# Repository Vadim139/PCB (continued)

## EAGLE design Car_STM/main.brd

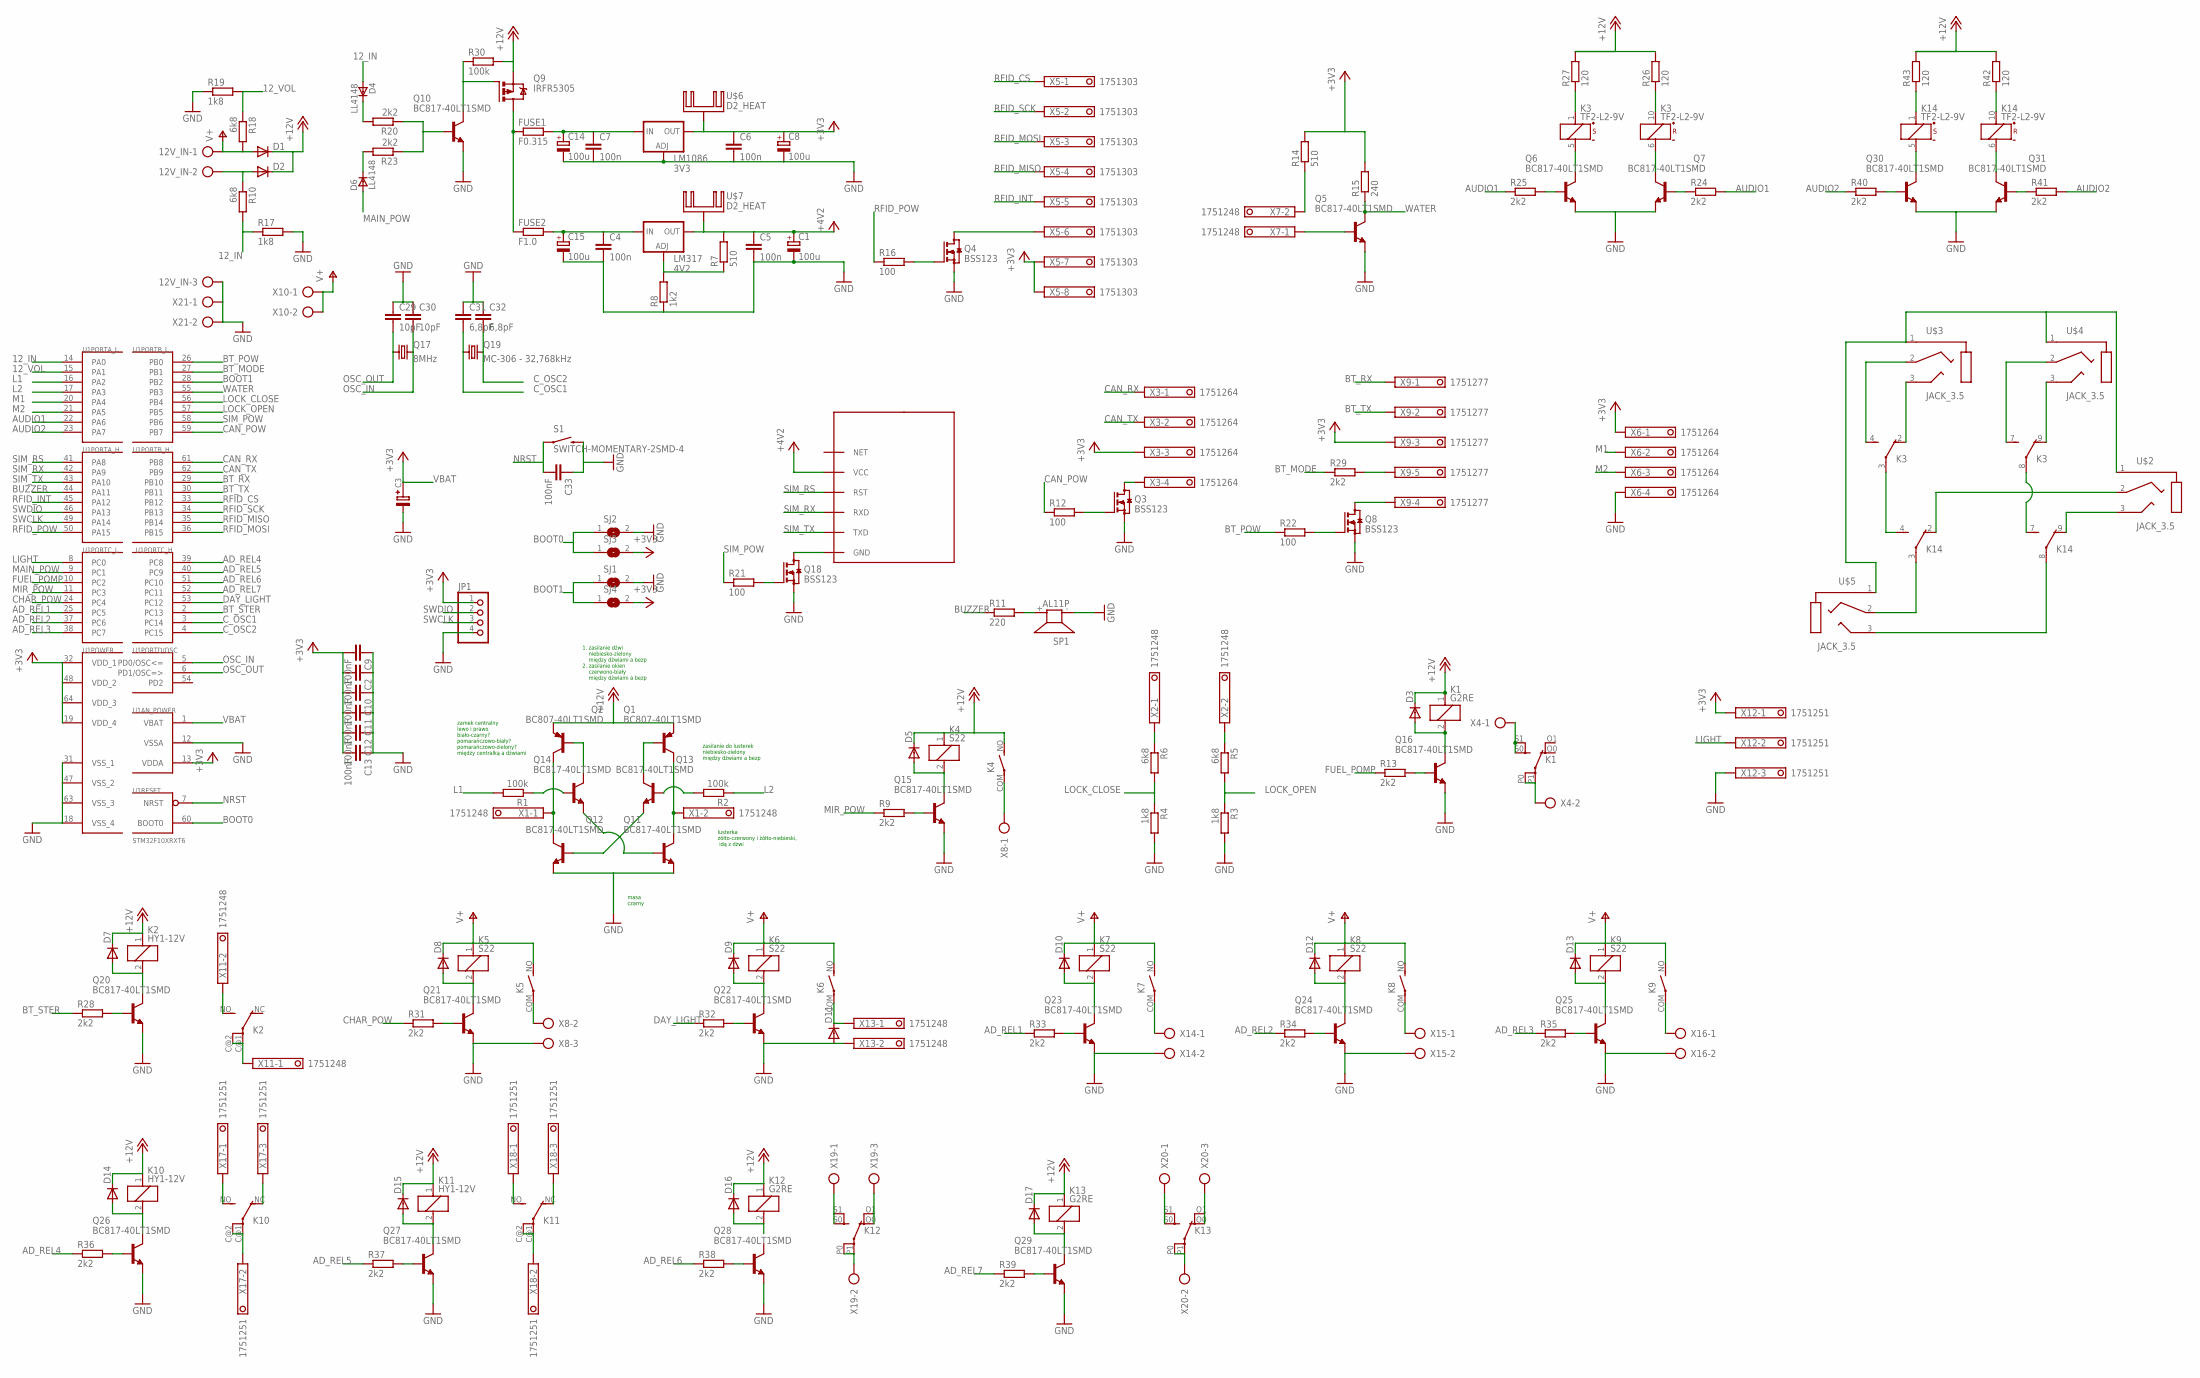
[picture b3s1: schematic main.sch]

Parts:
12V_IN: AK500/3
C1, C8, C14, C15: 100u; E2,5-6E
C2, C9, C10, C11, C12, C13, C33: 100nF; C2012
C3: CAP-13,5; PAC-G-1
C4, C5, C6, C7: 100n; C2012
C29, C30: 10pF; C2012
C31, C32: 6,8pF; C2012
D1, D2: DIODE-P6-15; P6-15
D3, D5, D7, D8, D9, D10, D11, D12, D13, D14, D15, D16, D17: DIODE-DO-214AC; DO-214AC
D4, D6: LL4148; SOD80_DO213AA_MINIMELF
FUSE1: F0.315; R2512
FUSE2: F1.0; R2512
JP1: PINHD-1X4; 1X04
K1, K12, K13: G2RE
K2, K10, K11: HY1-12V; HY
K3, K14: TF2-L2-9V; TF2
K4, K5, K6, K7, K8, K9: S22; LD
LM317: 4V2; D2PACK
LM1086: 3V3; D2PACK
Q1, Q2: BC807-40LT1SMD; SOT23-BEC
Q3, Q4, Q8, Q18: BSS123; SOT23
Q5, Q6, Q7, Q10, Q11, Q12, Q13, Q14, Q15, Q16, Q20, Q21, Q22, Q23, Q24, Q25, Q26, Q27, Q28, Q29, Q30, Q31: BC817-40LT1SMD; SOT23-BEC
Q9: IRFR5305; D-PAK_TO252AA
Q17: 8MHz; HC49UP
Q19: MC-306 - 32,768kHz; MC-306
R1, R2, R30: 100k; R0805
R3, R4, R17, R19: 1k8; R0805
R5, R6, R10, R18: 6k8; R0805
R7: 510; 0204/7
R8: 1k2; 0204/7
R9, R13, R20, R23, R24, R25, R28, R29, R31, R32, R33, R34, R35, R36, R37, R38, R39, R40, R41: 2k2; R0805
R11: 220; 0204/7
R12, R16, R21, R22: 100; R0805
R14: 510; R0805
R15: 240; R0805
R26, R27, R42, R43: 120; R0805
S1: SWITCH-MOMENTARY-2SMD-4; TACTILE_SWITCH_TALL
SJ1, SJ2, SJ3, SJ4: SJ
SP1: AL11P
U1: STM32F10XRXT6; TQFP64
U$1: SIM800L; SIM-CORE
U$2, U$3, U$4, U$5: JACK_3.5; STX3100
U$6, U$7: D2_HEAT; D2PACK_HEATSINK
X1, X2, X7, X11, X13: 1751248
X3, X6: 1751264
X4, X10, X14, X15, X16, X21: AK500/2
X5: 1751303
X8, X19, X20: AK500/3
X9: 1751277
X12, X17, X18: 1751251

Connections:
4V2: U$1.VCC
12_IN: D4.A, R10.2, R17.1, U1.14 (PA0)
12_VOL: R18.1, R19.2, U1.15 (PA1)
+3V3: C2.2, C6.1, C8.+, C9.2, C10.2, C11.2, C12.2, C13.2, JP1.1, LM1086.2 (OUT), R14.2, R15.2, SJ3.2, SJ4.2, U1.13 (VDDA), U1.19 (VDD_4), U1.32 (VDD_1), U1.48 (VDD_2), U1.64 (VDD_3), U$6.1, X3.3, X5.7, X5.8, X6.1, X9.3, X12.1
+12V: D1.C, D2.C, D3.C, D5.C, D7.C, D14.C, D15.C, D16.C, D17.C, K1.1, K2.1, K4.1, K4.NO (S), K10.1, K11.1, K12.1, K13.1, Q1.E, Q2.E, Q9.3 (S), R26.2, R27.2, R30.2, R42.2, R43.2
AD_REL1: R33.1, U1.25 (PC5)
AD_REL2: R34.1, U1.37 (PC6)
AD_REL3: R35.1, U1.38 (PC7)
AD_REL4: R36.1, U1.39 (PC8)
AD_REL5: R37.1, U1.40 (PC9)
AD_REL6: R38.1, U1.51 (PC10)
AD_REL7: R39.1, U1.52 (PC11)
AUDIO1: R24.2, R25.1, U1.22 (PA6)
AUDIO2: R40.1, R41.2, U1.23 (PA7)
BOOT0: SJ2.1, SJ3.1, U1.60 (BOOT0)
BOOT1: SJ1.1, SJ4.1, U1.28 (PB2)
BT_MODE: R29.1, U1.27 (PB1)
BT_POW: R22.1, U1.26 (PB0)
BT_RX: U1.29 (PB10), X9.1
BT_STER: R28.1, U1.2 (PC13)
BT_TX: U1.30 (PB11), X9.2
BUZZER: R11.1, U1.44 (PA11)
CAN_POW: R12.1, U1.59 (PB7)
CAN_RX: U1.61 (PB8), X3.1
CAN_TX: U1.62 (PB9), X3.2
CHAR_POW: R31.1, U1.24 (PC4)
C_OSC1: C31.2, Q19.1, U1.3 (PC14)
C_OSC2: C32.2, Q19.4 (2), U1.4 (PC15)
DAY_LIGHT: R32.1, U1.53 (PC12)
FUEL_POMP: R13.1, U1.10 (PC2)
GND: 12V_IN.3, C1.-, C2.1, C3.-, C4.2, C5.2, C6.2, C7.2, C8.-, C9.1, C10.1, C11.1, C12.1, C13.1, C14.-, C15.-, C29.1, C30.1, C31.1, C32.1, C33.1, D11.A, JP1.4, LM1086.1 (ADJ), Q3.2 (S), Q4.2 (S), Q5.E, Q6.E, Q7.E, Q8.2 (S), Q10.E, Q11.E, Q12.E, Q15.E, Q16.E, Q18.2 (S), Q20.E, Q21.E, Q22.E, Q23.E, Q24.E, Q25.E, Q26.E, Q27.E, Q28.E, Q29.E, Q30.E, Q31.E, R3.2, R4.2, R8.1, R17.2, R19.1, S1.B2 (2), SJ1.2, SJ2.2, SP1.- (1), U1.12 (VSSA), U1.18 (VSS_4), U1.31 (VSS_1), U1.47 (VSS_2), U1.63 (VSS_3), X6.4, X8.3, X12.3, X13.2, X14.2, X15.2, X16.2, X21.1, X21.2
L1: R1.2, U1.16 (PA2)
L2: R2.1, U1.17 (PA3)
LIGHT: U1.8 (PC0), X12.2
LOCK_CLOSE: R4.1, R6.2, U1.56 (PB4)
LOCK_OPEN: R3.1, R5.2, U1.57 (PB5)
M1: U1.20 (PA4), X6.2
M2: U1.21 (PA5), X6.3
MAIN_POW: D6.A, U1.9 (PC1)
MIR_POW: R9.1, U1.11 (PC3)
unnamed: 12V_IN.2, D2.A, R10.1
unnamed: R6.1, X2.1
unnamed: Q1.C, Q11.C, X1.2
unnamed: Q2.C, Q12.C, X1.1
unnamed: R5.1, X2.2
unnamed: Q2.B, Q14.C
unnamed: Q1.B, Q13.C
unnamed: Q12.B, Q13.E
unnamed: D4.C, R20.2
unnamed: R11.2, SP1.+ (2)
unnamed: Q3.1 (G), R12.2
unnamed: Q8.1 (G), R22.2
unnamed: LM317.1 (ADJ), R7.1, R8.2
unnamed: Q3.3 (D), X3.4
unnamed: D3.A, K1.2, Q16.C
unnamed: Q16.B, R13.2
unnamed: K1.S0 (S), K1.S1 (S), X4.1
unnamed: K1.P0, K1.P1, X4.2
unnamed: R14.1, X7.2
unnamed: Q4.3 (D), X5.6
unnamed: K14.1 (+), R43.1
unnamed: Q14.B, R1.1
unnamed: Q5.B, X7.1
unnamed: Q13.B, R2.2
unnamed: Q11.B, Q14.E
unnamed: Q4.1 (G), R16.2
unnamed: Q15.B, R9.2
unnamed: D5.A, K4.2, Q15.C
unnamed: K14.10 (+), R42.1
unnamed: K14.5 (-), Q30.C
unnamed: K14.6 (-), Q31.C
unnamed: Q30.B, R40.2
unnamed: K3.1 (+), R27.1
unnamed: K3.10 (+), R26.1
unnamed: K3.5 (-), Q6.C
unnamed: K3.6 (-), Q7.C
unnamed: Q6.B, R25.2
unnamed: Q8.3 (D), X9.4
unnamed: FUSE1.1, FUSE2.1, Q9.4 (D)
unnamed: Q7.B, R24.1
unnamed: R29.2, X9.5
unnamed: Q10.B, R20.1, R23.1
unnamed: Q9.1 (G), Q10.C, R30.1
unnamed: D6.C, R23.2
unnamed: C7.1, C14.+, FUSE1.2, LM1086.3 (IN)
unnamed: Q18.3 (D), U$1.GND
unnamed: K4.COM, X8.1
unnamed: C4.1, C15.+, FUSE2.2, LM317.3 (IN)
unnamed: Q31.B, R41.1
unnamed: Q18.1 (G), R21.2
unnamed: D7.A, K2.2, Q20.C
unnamed: Q20.B, R28.2
unnamed: D11.C, K6.COM, X13.1
unnamed: Q26.B, R36.2
unnamed: D8.A, K5.2, Q21.C
unnamed: K2.NO (S), X11.2
unnamed: K2.C@1, K2.C@2, X11.1
unnamed: Q21.B, R31.2
unnamed: D9.A, K6.2, Q22.C
unnamed: Q22.B, R32.2
unnamed: D10.A, K7.2, Q23.C
unnamed: Q23.B, R33.2
unnamed: K5.COM, X8.2
unnamed: K7.COM, X14.1
unnamed: D14.A, K10.2, Q26.C
unnamed: D12.A, K8.2, Q24.C
unnamed: Q24.B, R34.2
unnamed: K8.COM, X15.1
unnamed: Q27.B, R37.2
unnamed: D13.A, K9.2, Q25.C
unnamed: Q25.B, R35.2
unnamed: K9.COM, X16.1
unnamed: D15.A, K11.2, Q27.C
unnamed: Q28.B, R38.2
unnamed: K10.NO (S), X17.1
unnamed: Q29.B, R39.2
unnamed: D17.A, K13.2, Q29.C
unnamed: K10.NC (O), X17.3
unnamed: D16.A, K12.2
unnamed: K10.C@1, K10.C@2, X17.2
unnamed: K11.NO (S), X18.1
unnamed: K11.NC (O), X18.3
unnamed: K11.C@1, K11.C@2, X18.2
unnamed: K12.S0 (S), K12.S1 (S), X19.1
unnamed: K12.O0 (O), K12.O1 (O), X19.3
unnamed: K12.P0, K12.P1, X19.2
unnamed: K13.S0 (S), K13.S1 (S), X20.1
unnamed: K13.O0 (O), K13.O1 (O), X20.3
unnamed: K13.P0, K13.P1, X20.2
unnamed: K14.2 (O), U$2.2
unnamed: K14.9 (O), U$2.3 (5)
unnamed: K3.8, K14.7 (S)
unnamed: K3.3, K14.4 (S)
unnamed: K3.4 (S), U$3.2
unnamed: K3.2 (O), U$3.3 (5)
unnamed: K3.7 (S), U$4.2
unnamed: K3.9 (O), U$4.3 (5)
unnamed: U$2.1, U$3.1, U$4.1, U$5.1
unnamed: K14.3, U$5.2
unnamed: K14.8, U$5.3 (5)
NRST: C33.2, S1.A2 (1), U1.7 (NRST)
OSC_IN: C30.2, Q17.2, U1.5 (PD0/OSC<=)
OSC_OUT: C29.2, Q17.1, U1.6 (PD1/OSC=>)
RFID_CS: U1.33 (PB12), X5.1
RFID_INT: U1.45 (PA12), X5.5
RFID_MISO: U1.35 (PB14), X5.4
RFID_MOSI: U1.36 (PB15), X5.3
RFID_POW: R16.1, U1.50 (PA15)
RFID_SCK: U1.34 (PB13), X5.2
SIM_POW: R21.1, U1.58 (PB6)
SIM_RS: U1.41 (PA8), U$1.RST
SIM_RX: U1.42 (PA9), U$1.RXD
SIM_TX: U1.43 (PA10), U$1.TXD
SWCLK: JP1.3, U1.49 (PA14)
SWDIO: JP1.2, U1.46 (PA13)
V+: 12V_IN.1, D1.A, D8.C, D9.C, D10.C, D12.C, D13.C, K5.1, K5.NO (S), K6.1, K6.NO (S), K7.1, K7.NO (S), K8.1, K8.NO (S), K9.1, K9.NO (S), R18.2, X10.1, X10.2
VBAT: C3.+, U1.1 (VBAT)
VCC: C1.+, C5.1, LM317.2 (OUT), R7.2, U$7.1
WATER: Q5.C, R15.1, U1.55 (PB3)

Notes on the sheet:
lusterka żółto-czerwony i żółto-niebieski, idą z dżwi
zasilanie do lusterek niebiesko-zielony między dżwiami a bezp
1. zasilanie dżwi niebiesko-zielony między dżwiami a bezp 2. zasilanie okien czerwono-biały między dżwiami a bezp
zamek centralny lewo i prawo biało-czarny? pomarańczowo-biały? pomarańczowo-zielony? między centralką a dżwiami
masa czarny

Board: 2 copper layers, 166 parts (8 on the bottom side), 158 nets, no tracks yet.

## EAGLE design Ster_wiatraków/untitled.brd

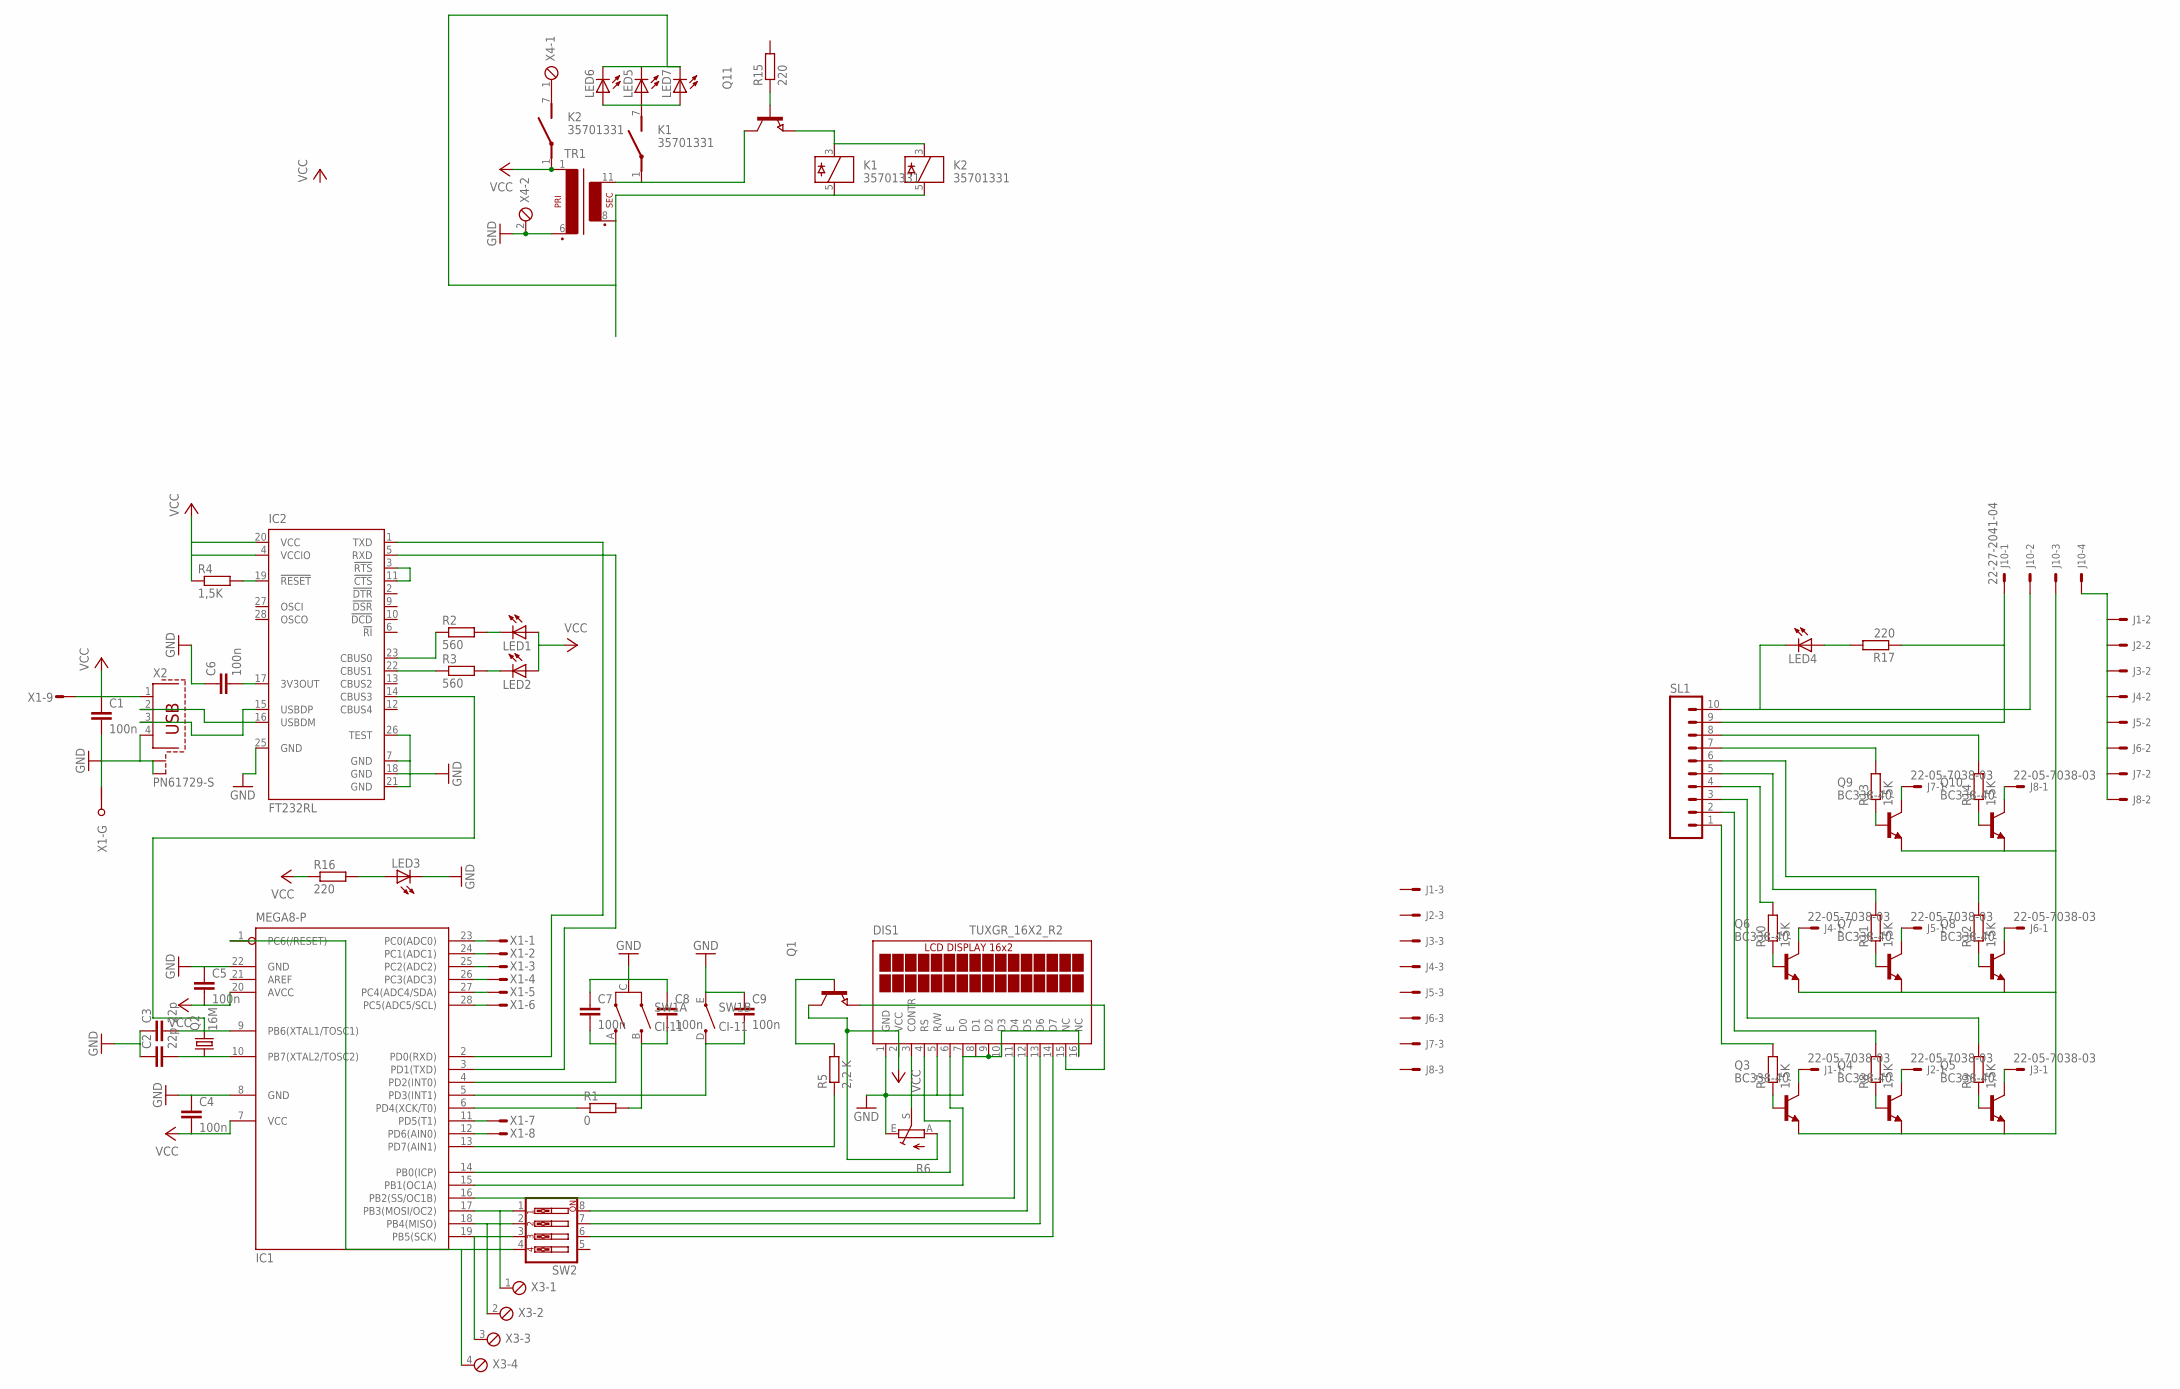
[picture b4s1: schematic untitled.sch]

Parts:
C1, C4, C5, C6: 100n; C0603
C2, C3: 22p; C050-024X044
C7, C8, C9: 100n; C050-024X044
DIS1: TUXGR_16X2_R2
IC1: MEGA8-P; DIL28-3
IC2: FT232RL; SSOP28
J1, J2, J3, J4, J5, J6, J7, J8: 22-05-7038-03; 7395-03
J10: 22-27-2041-04; 6410-04
K1, K2: 35701331; REED
LED1, LED2: LEDCHIPLED_0805; CHIPLED_0805
LED3, LED4, LED5, LED6, LED7: LED5MM
Q1, Q11: NPN-TRANSISTOR_SOT23; SOT23
Q2: 16M; HC49U-V
Q3, Q4, Q5, Q6, Q7, Q8, Q9, Q10: BC338-40; TO92-EBC
R1: 0; M1206
R2, R3: 560; M1406
R4, R7, R8, R9, R10, R11, R12, R13, R14: 1,5K; 0204/5
R5: 2,2 K; 0204/7
R6: TRIM_EU-CA6V; CA6V
R15, R16, R17: 220; 0204/7
SL1: M10; 10P
SW1: CI-11
SW2: SW_DIP-4; EDG-04
TR1: EI48-1
X1: M09VPS; M09VP
X2: PN61729-S
X3, X4: MPT4; 4POL254

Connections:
GND: C1.2, C2.1, C3.1, C4.1, C5.1, C6.1, C7.1, C8.1, C9.1, DIS1.1 (GND), DIS1.5 (R/W), DIS1.7 (D0), DIS1.8 (D1), DIS1.9 (D2), DIS1.10 (D3), DIS1.16 (NC), IC1.8 (GND), IC1.22 (GND), IC2.7 (GND), IC2.18 (GND), IC2.21 (GND), IC2.25 (GND), IC2.26 (TEST), LED3.K (C), R6.E, SW1.C, SW1.E, TR1.6 (P2), X1.G1, X2.4, X2.S1, X2.S2, X4.2
unnamed: IC1.11 (PD5(T1)), X1.7 (M)
unnamed: IC1.6 (PD4(XCK/T0)), R1.1
unnamed: LED5.K (C), LED6.K (C), LED7.K (C)
unnamed: Q11.1 (B), R15.1
unnamed: K1.1, Q11.3 (C), TR1.11 (S4)
unnamed: K1.3, K2.3, Q11.2 (E)
unnamed: K1.5, K2.5, TR1.8 (S3)
unnamed: IC2.16 (USBDM), X2.2
unnamed: IC2.15 (USBDP), X2.3
unnamed: DIS1.3 (CONTR), R6.S
unnamed: DIS1.4 (RS), IC1.14 (PB0(ICP))
unnamed: DIS1.6 (E), IC1.15 (PB1(OC1A))
unnamed: DIS1.11 (D4), IC1.16 (PB2(SS/OC1B))
unnamed: DIS1.12 (D5), SW2.8
unnamed: DIS1.13 (D6), SW2.7
unnamed: DIS1.14 (D7), SW2.6
unnamed: IC1.13 (PD7(AIN1)), R5.1
unnamed: Q1.1 (B), R5.2
unnamed: DIS1.15 (NC), Q1.2 (E)
unnamed: C3.2, IC1.9 (PB6(XTAL1/TOSC1)), IC2.14 (CBUS3), Q2.2
unnamed: C6.2, IC2.17 (3V3OUT)
unnamed: C2.2, IC1.10 (PB7(XTAL2/TOSC2)), Q2.1
unnamed: LED1.C, R2.2
unnamed: LED2.C, R3.2
unnamed: IC2.19 (!RESET), R4.2
unnamed: IC2.23 (CBUS0), R2.1
unnamed: IC2.22 (CBUS1), R3.1
unnamed: IC2.3 (!RTS), IC2.11 (!CTS)
unnamed: IC1.2 (PD0(RXD)), IC2.1 (TXD)
unnamed: IC1.3 (PD1(TXD)), IC2.5 (RXD)
unnamed: IC1.1 (PC6(/RESET)), SW2.4, X3.4
unnamed: IC1.23 (PC0(ADC0)), X1.1 (M)
unnamed: IC1.24 (PC1(ADC1)), X1.2 (M)
unnamed: IC1.25 (PC2(ADC2)), X1.3 (M)
unnamed: IC1.26 (PC3(ADC3)), X1.4 (M)
unnamed: IC1.27 (PC4(ADC4/SDA)), X1.5 (M)
unnamed: IC1.28 (PC5(ADC5/SCL)), X1.6 (M)
unnamed: IC1.12 (PD6(AIN0)), X1.8 (M)
unnamed: IC1.17 (PB3(MOSI/OC2)), SW2.1, X3.1
unnamed: IC1.18 (PB4(MISO)), SW2.2, X3.2
unnamed: IC1.19 (PB5(SCK)), SW2.3, X3.3
unnamed: K1.7 (S), LED5.A, LED6.A, LED7.A
unnamed: C9.2, IC1.5 (PD3(INT1)), SW1.D
unnamed: C7.2, IC1.4 (PD2(INT0)), SW1.A
unnamed: C8.2, R1.2, SW1.B
unnamed: J1.1, Q3.C
unnamed: J2.1, Q4.C
unnamed: K2.7 (S), X4.1
unnamed: LED3.A, R16.2
unnamed: J10.1, R17.1, SL1.9
unnamed: LED4.A, R17.2
unnamed: J10.2, LED4.K (C), SL1.10
unnamed: J3.1, Q5.C
unnamed: J6.1, Q8.C
unnamed: J5.1, Q7.C
unnamed: J4.1, Q6.C
unnamed: J7.1, Q9.C
unnamed: J8.1, Q10.C
unnamed: R7.2, SL1.1
unnamed: Q3.B, R7.1
unnamed: R8.2, SL1.2
unnamed: Q4.B, R8.1
unnamed: R9.2, SL1.3
unnamed: R10.2, SL1.4
unnamed: R11.2, SL1.5
unnamed: R12.2, SL1.6
unnamed: R13.2, SL1.7
unnamed: R14.2, SL1.8
unnamed: Q9.B, R13.1
unnamed: Q10.B, R14.1
unnamed: Q8.B, R12.1
unnamed: Q7.B, R11.1
unnamed: Q6.B, R10.1
unnamed: Q5.B, R9.1
unnamed: J1.2, J2.2, J3.2, J4.2, J5.2, J6.2, J7.2, J8.2, J10.4
unnamed: J10.3, Q3.E, Q4.E, Q5.E, Q6.E, Q7.E, Q8.E, Q9.E, Q10.E
VCC: C1.1, C4.2, C5.2, DIS1.2 (VCC), IC1.7 (VCC), IC1.20 (AVCC), IC2.4 (VCCIO), IC2.20 (VCC), K2.1, LED1.A, LED2.A, Q1.3 (C), R4.1, R6.A, R16.1, TR1.1, X1.9 (M), X2.1

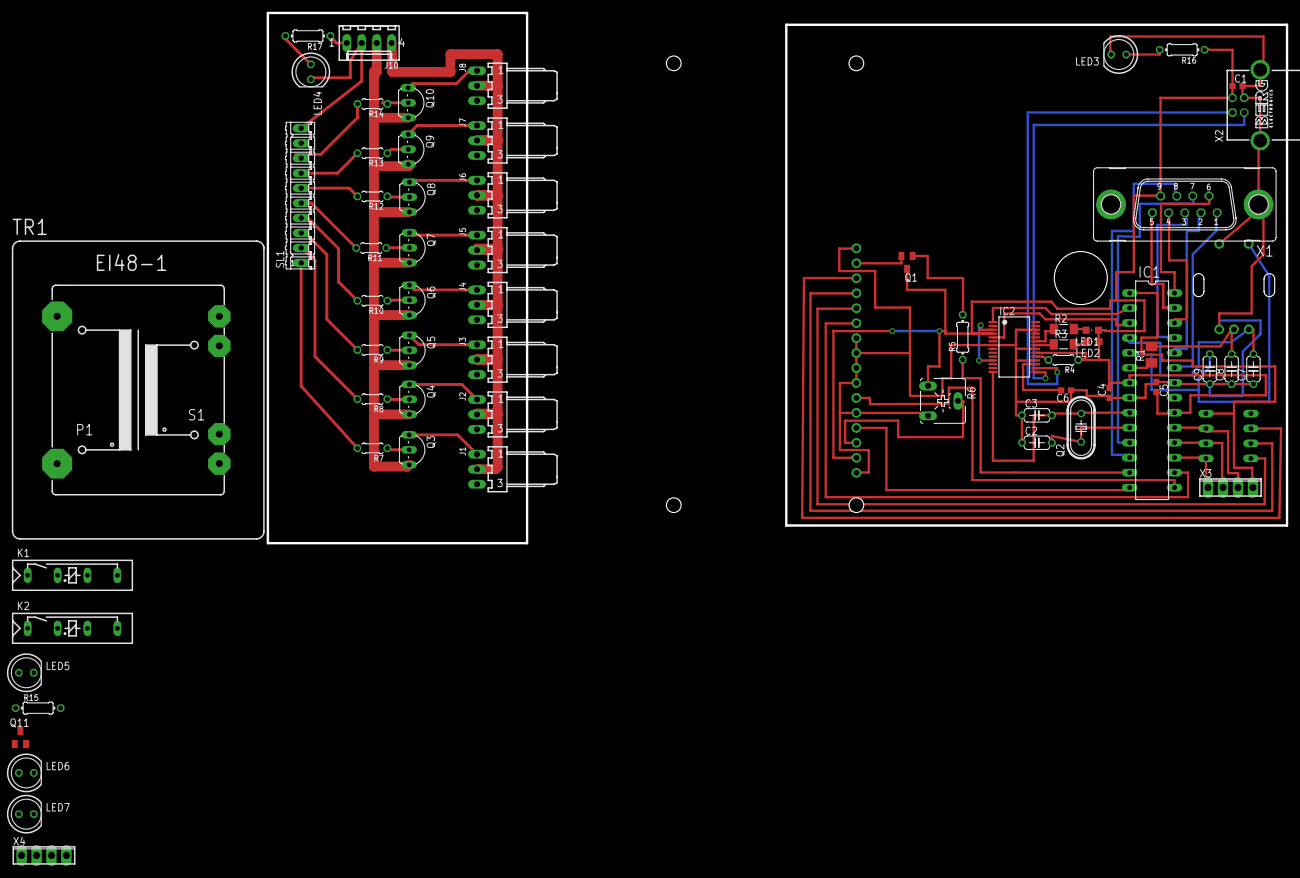
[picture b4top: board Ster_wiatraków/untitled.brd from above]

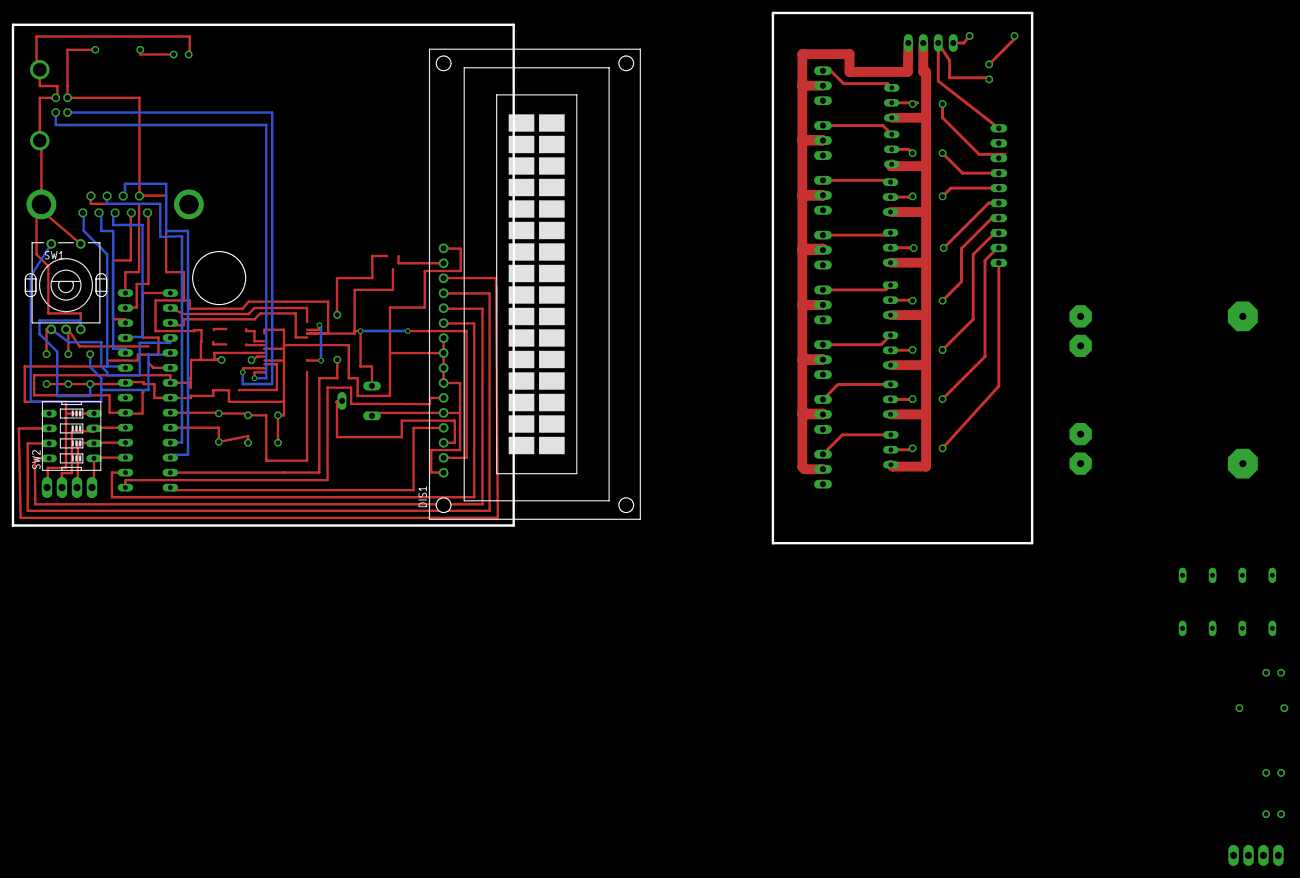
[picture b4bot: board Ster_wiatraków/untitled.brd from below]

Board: 2 copper layers, 173.0 x 90.0 mm, 66 parts (3 on the bottom side), 78 nets.

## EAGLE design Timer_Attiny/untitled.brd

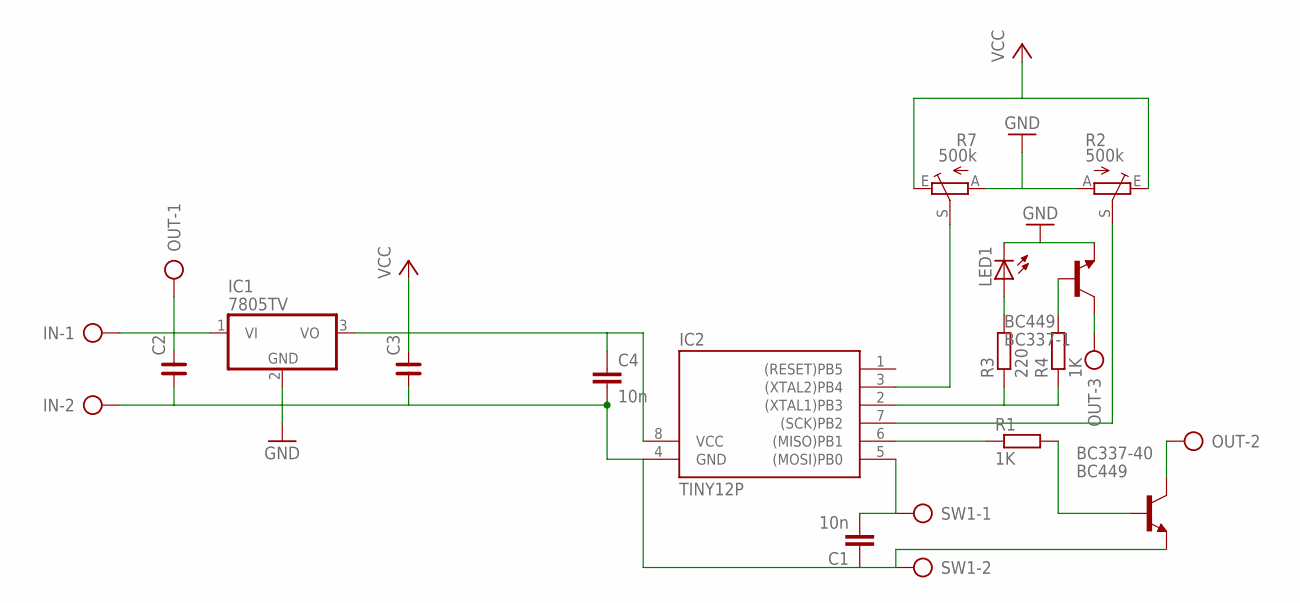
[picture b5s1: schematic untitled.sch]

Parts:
BC337-1, BC337-40: BC449; TO92-EBC
C1, C4: 10n; C050-024X044
C2, C3: C_1206; C1206
IC1: 7805TV; TO220V
IC2: TINY12P; DIL08
IN: AK500/2
LED1: LED3MM
OUT: AK500/3
R1, R4: 1K; M1206
R2, R7: 500k; CA6V
R3: 220; M1206
SW1: AK500/2

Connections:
GND: BC337-1.E, BC337-40.E, C1.1, C2.1, C3.1, C4.2, IC1.2 (GND), IC2.4 (GND), IN.2, LED1.K (C), R2.A, R7.A, SW1.2
unnamed: BC337-1.B, R4.2
unnamed: C2.2, IC1.1 (VI), IN.1, OUT.1
unnamed: BC337-40.C, OUT.2
unnamed: C1.2, IC2.5 ((MOSI)PB0), SW1.1
unnamed: BC337-1.C, OUT.3
unnamed: IC2.6 ((MISO)PB1), R1.1
unnamed: BC337-40.B, R1.2
unnamed: IC2.7 ((SCK)PB2), R2.S
unnamed: IC2.3 ((XTAL2)PB4), R7.S
unnamed: LED1.A, R3.2
unnamed: IC2.2 ((XTAL1)PB3), R3.1, R4.1
VCC: C3.2, C4.1, IC1.3 (VO), IC2.8 (VCC), R2.E, R7.E

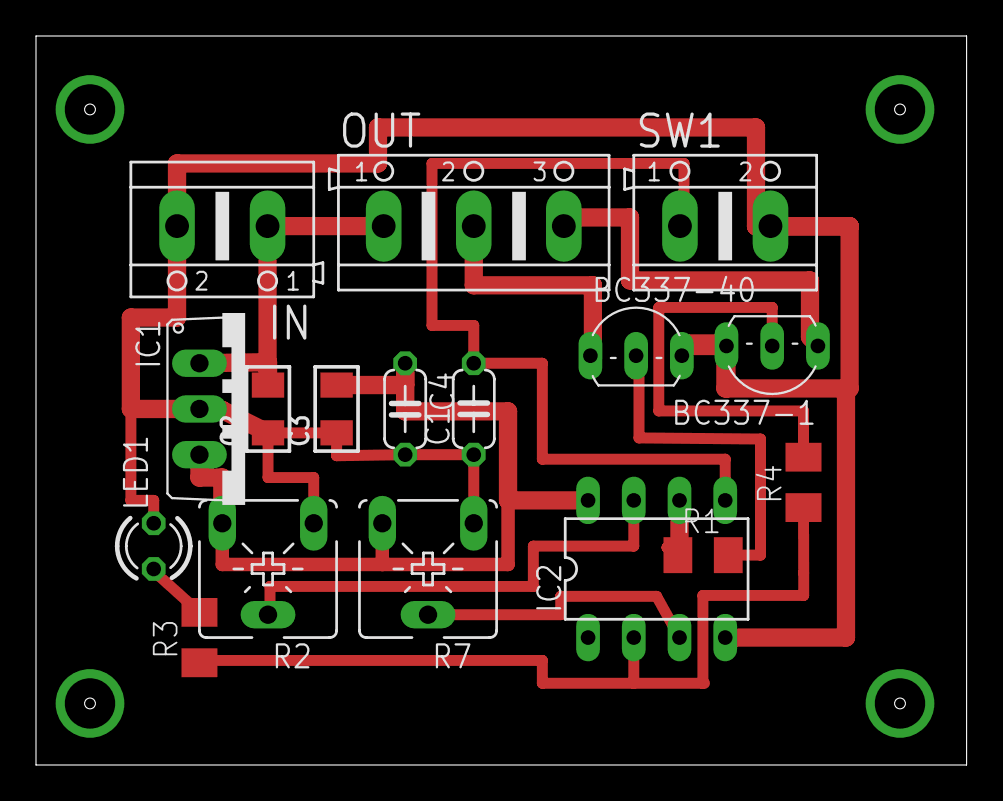
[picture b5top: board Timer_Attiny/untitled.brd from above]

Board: 2 copper layers, 51.7 x 40.5 mm, 17 parts (0 on the bottom side), 13 nets.

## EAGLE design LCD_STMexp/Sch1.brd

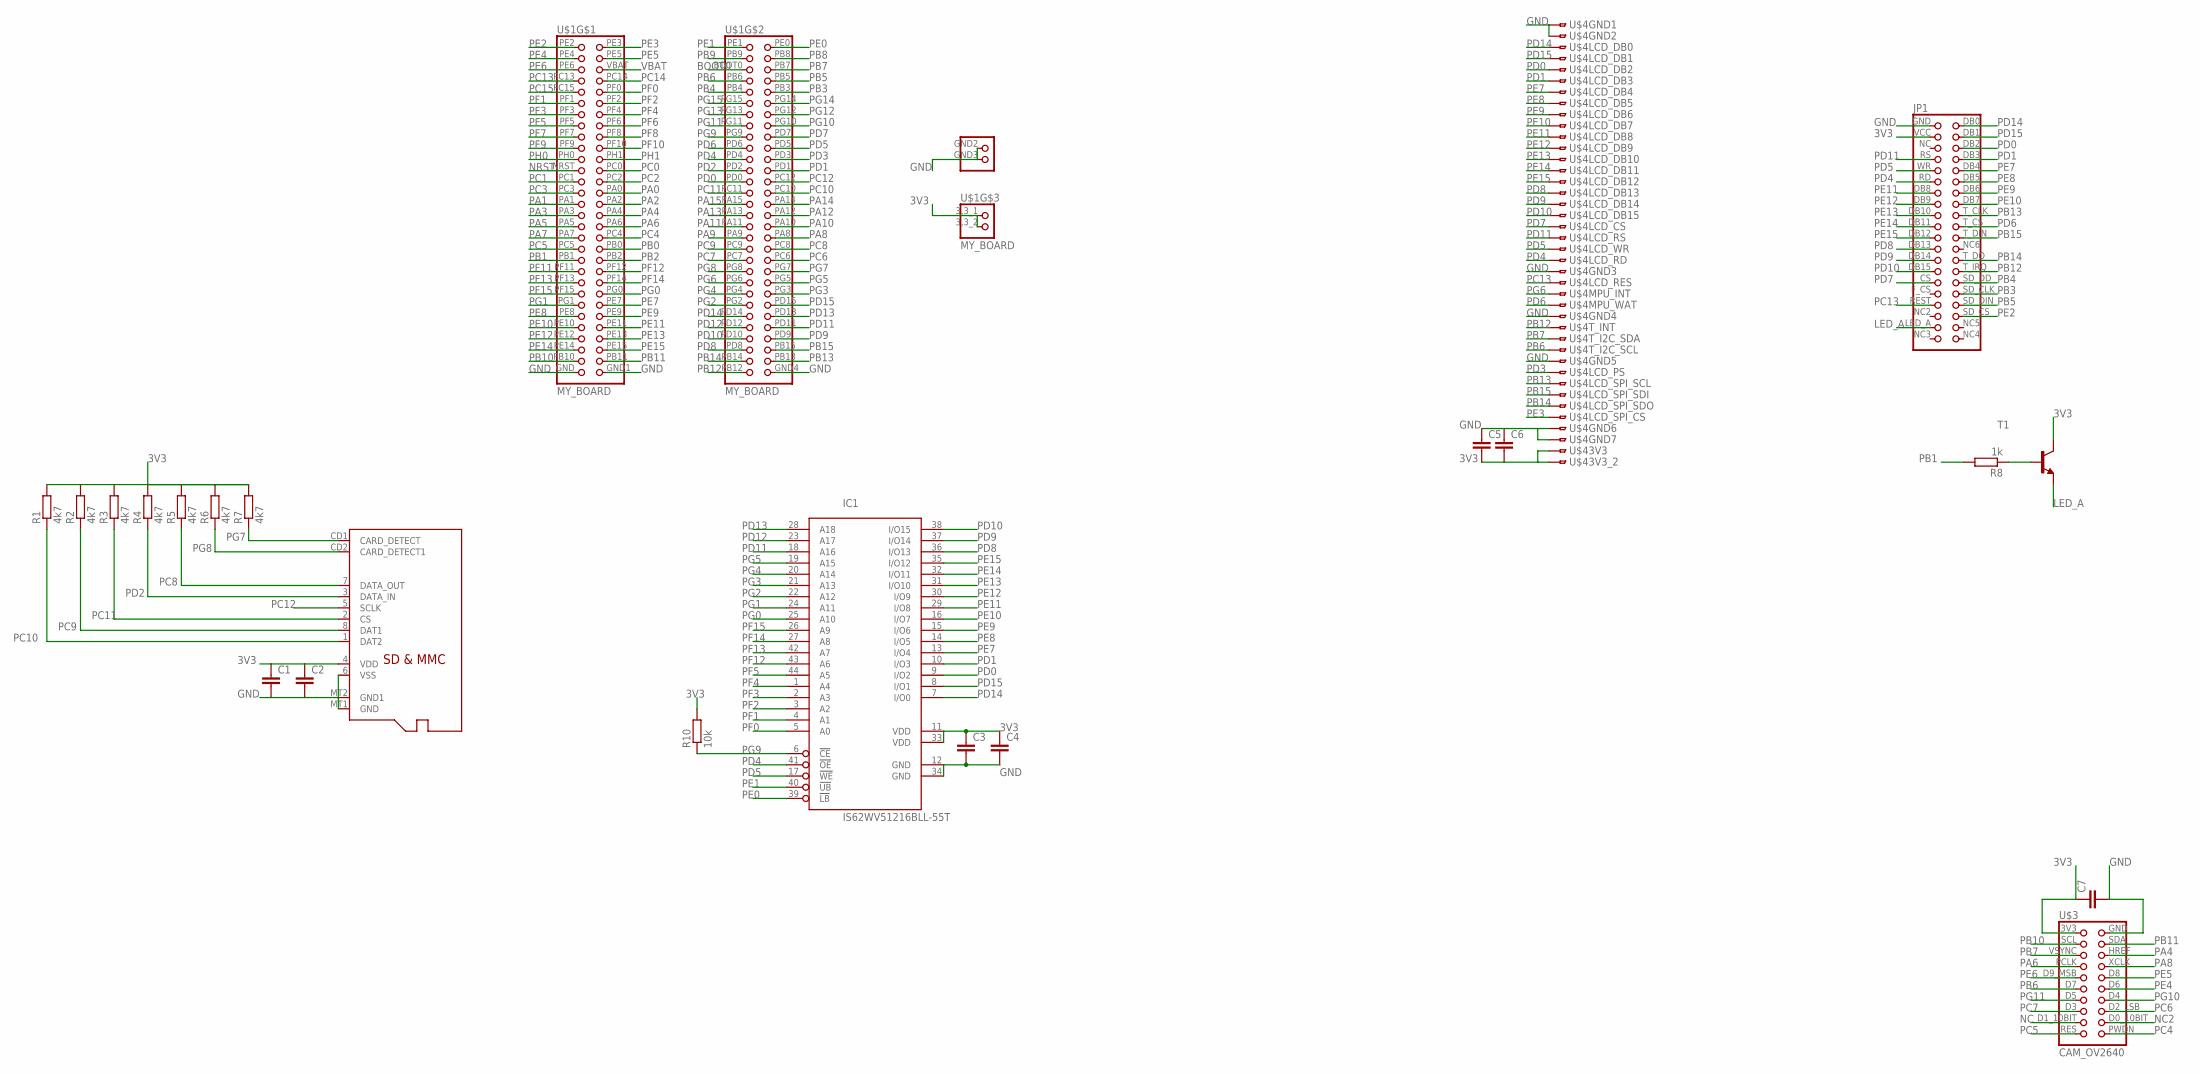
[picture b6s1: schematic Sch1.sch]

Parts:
C1, C2, C3, C4, C5, C6, C7: C-EUC1206; C1206
IC1: IS62WV51216BLL-55T; TSOP-II-44
JP1: LCD320QVBLCD320QVB; 2X20
R1, R2, R3, R4, R5, R6, R7: 4k7; 0204/7
R8: 1k; 0204/5
R10: 10k; 0204/7
T1: BC337-NPN-TO92-CBE; TO92-CBE
U$1: MY_BOARD
U$3: CAM_OV2640
U$4: LCD800TFT; FH12-40S-0.5SH
U$5: MICROSD

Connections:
3V3: C1.1, C2.1, C3.1, C4.1, C5.2, C6.2, C7.1, IC1.11 (VDD), IC1.33 (VDD), JP1.VCC (3), R1.2, R2.2, R3.2, R4.2, R5.2, R6.2, R7.2, R10.2, T1.C, U$1.3,3_1 (1), U$1.3,3_2 (2), U$3.3V3, U$4.39, U$4.40, U$5.4 (VDD)
BOOT0: U$1.BOOT0 (5)
GND: C1.2, C2.2, C3.2, C4.2, C5.1, C6.1, C7.2, IC1.12 (GND), IC1.34 (GND), JP1.GND (1), U$1.GND (59), U$1.GND1 (60), U$1.GND2 (3), U$1.GND3 (4), U$1.GND4 (60), U$3.GND, U$4.1, U$4.2, U$4.23, U$4.27, U$4.31, U$4.37, U$4.38, U$5.6 (VSS), U$5.MT1 (GND), U$5.MT2 (GND1)
LED_A: JP1.LED_A (37), T1.E
unnamed: R8.1, T1.B
NC: U$3.D1_10BIT
NC2: U$3.D0_10BIT
NRST: U$1.NRST (23)
PA0: U$1.PA0 (28)
PA1: U$1.PA1 (29)
PA2: U$1.PA2 (30)
PA3: U$1.PA3 (31)
PA4: U$1.PA4 (32), U$3.HREF
PA5: U$1.PA5 (33)
PA6: U$1.PA6 (34), U$3.PCLK
PA7: U$1.PA7 (35)
PA8: U$1.PA8 (36), U$3.XCLK
PA9: U$1.PA9 (35)
PA10: U$1.PA10 (34)
PA11: U$1.PA11 (33)
PA12: U$1.PA12 (32)
PA13: U$1.PA13 (31)
PA14: U$1.PA14 (30)
PA15: U$1.PA15 (29)
PB0: U$1.PB0 (38)
PB1: R8.2, U$1.PB1 (39)
PB2: U$1.PB2 (40)
PB3: JP1.SD_CLK (32), U$1.PB3 (10)
PB4: JP1.SD_DD (30), U$1.PB4 (9)
PB5: JP1.SD_DIN (34), U$1.PB5 (8)
PB6: U$1.PB6 (7), U$3.D7, U$4.30
PB7: U$1.PB7 (6), U$3.VSYNC, U$4.29
PB8: U$1.PB8 (4)
PB9: U$1.PB9 (3)
PB10: U$1.PB10 (57), U$3.SCL
PB11: U$1.PB11 (58), U$3.SDA
PB12: JP1.T_IRQ (28), U$1.PB12 (59), U$4.28
PB13: JP1.T_CLK (18), U$1.PB13 (58), U$4.33
PB14: JP1.T_DO (26), U$1.PB14 (57), U$4.35
PB15: JP1.T_DIN (22), U$1.PB15 (56), U$4.34
PC0: U$1.PC0 (24)
PC1: U$1.PC1 (25)
PC2: U$1.PC2 (26)
PC3: U$1.PC3 (27)
PC4: U$1.PC4 (36), U$3.PWDN
PC5: U$1.PC5 (37), U$3.RES
PC6: U$1.PC6 (40), U$3.D2_LSB
PC7: U$1.PC7 (39), U$3.D3
PC8: R5.1, U$1.PC8 (38), U$5.7 (DATA_OUT)
PC9: R2.1, U$1.PC9 (37), U$5.8 (DAT1)
PC10: R1.1, U$1.PC10 (28), U$5.1 (DAT2)
PC11: R3.1, U$1.PC11 (27), U$5.2 (CS)
PC12: U$1.PC12 (26), U$5.5 (SCLK)
PC13: JP1.REST (33), U$1.PC13 (7), U$4.24
PC14: U$1.PC14 (8)
PC15: U$1.PC15 (9)
PD0: IC1.9 (I/O2), JP1.DB2 (6), U$1.PD0 (25), U$4.5
PD1: IC1.10 (I/O3), JP1.DB3 (8), U$1.PD1 (24), U$4.6
PD2: R4.1, U$1.PD2 (23), U$5.3 (DATA_IN)
PD3: U$1.PD3 (22), U$4.32
PD4: IC1.41 (!OE), JP1.RD (11), U$1.PD4 (21), U$4.22
PD5: IC1.17 (!WE), JP1.WR (9), U$1.PD5 (20), U$4.21
PD6: JP1.T_CS (20), U$1.PD6 (19), U$4.26
PD7: JP1.CS (29), U$1.PD7 (18), U$4.19
PD8: IC1.36 (I/O13), JP1.DB13 (23), U$1.PD8 (55), U$4.16
PD9: IC1.37 (I/O14), JP1.DB14 (25), U$1.PD9 (54), U$4.17
PD10: IC1.38 (I/O15), JP1.DB15 (27), U$1.PD10 (53), U$4.18
PD11: IC1.18 (A16), JP1.RS (7), U$1.PD11 (52), U$4.20
PD12: IC1.23 (A17), U$1.PD12 (51)
PD13: IC1.28 (A18), U$1.PD13 (50)
PD14: IC1.7 (I/O0), JP1.DB0 (2), U$1.PD14 (49), U$4.3
PD15: IC1.8 (I/O1), JP1.DB1 (4), U$1.PD15 (48), U$4.4
PE0: IC1.39 (!LB), U$1.PE0 (2)
PE1: IC1.40 (!UB), U$1.PE1 (1)
PE2: JP1.SD_CS (36), U$1.PE2 (1)
PE3: U$1.PE3 (2), U$4.36
PE4: U$1.PE4 (3), U$3.D6
PE5: U$1.PE5 (4), U$3.D8
PE6: U$1.PE6 (5), U$3.D9_MSB
PE7: IC1.13 (I/O4), JP1.DB4 (10), U$1.PE7 (48), U$4.7
PE8: IC1.14 (I/O5), JP1.DB5 (12), U$1.PE8 (49), U$4.8
PE9: IC1.15 (I/O6), JP1.DB6 (14), U$1.PE9 (50), U$4.9
PE10: IC1.16 (I/O7), JP1.DB7 (16), U$1.PE10 (51), U$4.10
PE11: IC1.29 (I/O8), JP1.DB8 (13), U$1.PE11 (52), U$4.11
PE12: IC1.30 (I/O9), JP1.DB9 (15), U$1.PE12 (53), U$4.12
PE13: IC1.31 (I/O10), JP1.DB10 (17), U$1.PE13 (54), U$4.13
PE14: IC1.32 (I/O11), JP1.DB11 (19), U$1.PE14 (55), U$4.14
PE15: IC1.35 (I/O12), JP1.DB12 (21), U$1.PE15 (56), U$4.15
PF0: IC1.5 (A0), U$1.PF0 (10)
PF1: IC1.4 (A1), U$1.PF1 (11)
PF2: IC1.3 (A2), U$1.PF2 (12)
PF3: IC1.2 (A3), U$1.PF3 (13)
PF4: IC1.1 (A4), U$1.PF4 (14)
PF5: IC1.44 (A5), U$1.PF5 (15)
PF6: U$1.PF6 (16)
PF7: U$1.PF7 (17)
PF8: U$1.PF8 (18)
PF9: U$1.PF9 (19)
PF10: U$1.PF10 (20)
PF11: U$1.PF11 (41)
PF12: IC1.43 (A6), U$1.PF12 (42)
PF13: IC1.42 (A7), U$1.PF13 (43)
PF14: IC1.27 (A8), U$1.PF14 (44)
PF15: IC1.26 (A9), U$1.PF15 (45)
PG0: IC1.25 (A10), U$1.PG0 (46)
PG1: IC1.24 (A11), U$1.PG1 (47)
PG2: IC1.22 (A12), U$1.PG2 (47)
PG3: IC1.21 (A13), U$1.PG3 (46)
PG4: IC1.20 (A14), U$1.PG4 (45)
PG5: IC1.19 (A15), U$1.PG5 (44)
PG6: U$1.PG6 (43), U$4.25
PG7: R7.1, U$1.PG7 (42), U$5.CD1 (CARD_DETECT)
PG8: R6.1, U$1.PG8 (41), U$5.CD2 (CARD_DETECT1)
PG9: IC1.6 (!CE), R10.1, U$1.PG9 (17)
PG10: U$1.PG10 (16), U$3.D4
PG11: U$1.PG11 (15), U$3.D5
PG12: U$1.PG12 (14)
PG13: U$1.PG13 (13)
PG14: U$1.PG14 (12)
PG15: U$1.PG15 (11)
PH0: U$1.PH0 (21)
PH1: U$1.PH1 (22)
VBAT: U$1.VBAT (6)

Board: 2 copper layers, 23 parts (0 on the bottom side), 83 nets, no tracks yet.
